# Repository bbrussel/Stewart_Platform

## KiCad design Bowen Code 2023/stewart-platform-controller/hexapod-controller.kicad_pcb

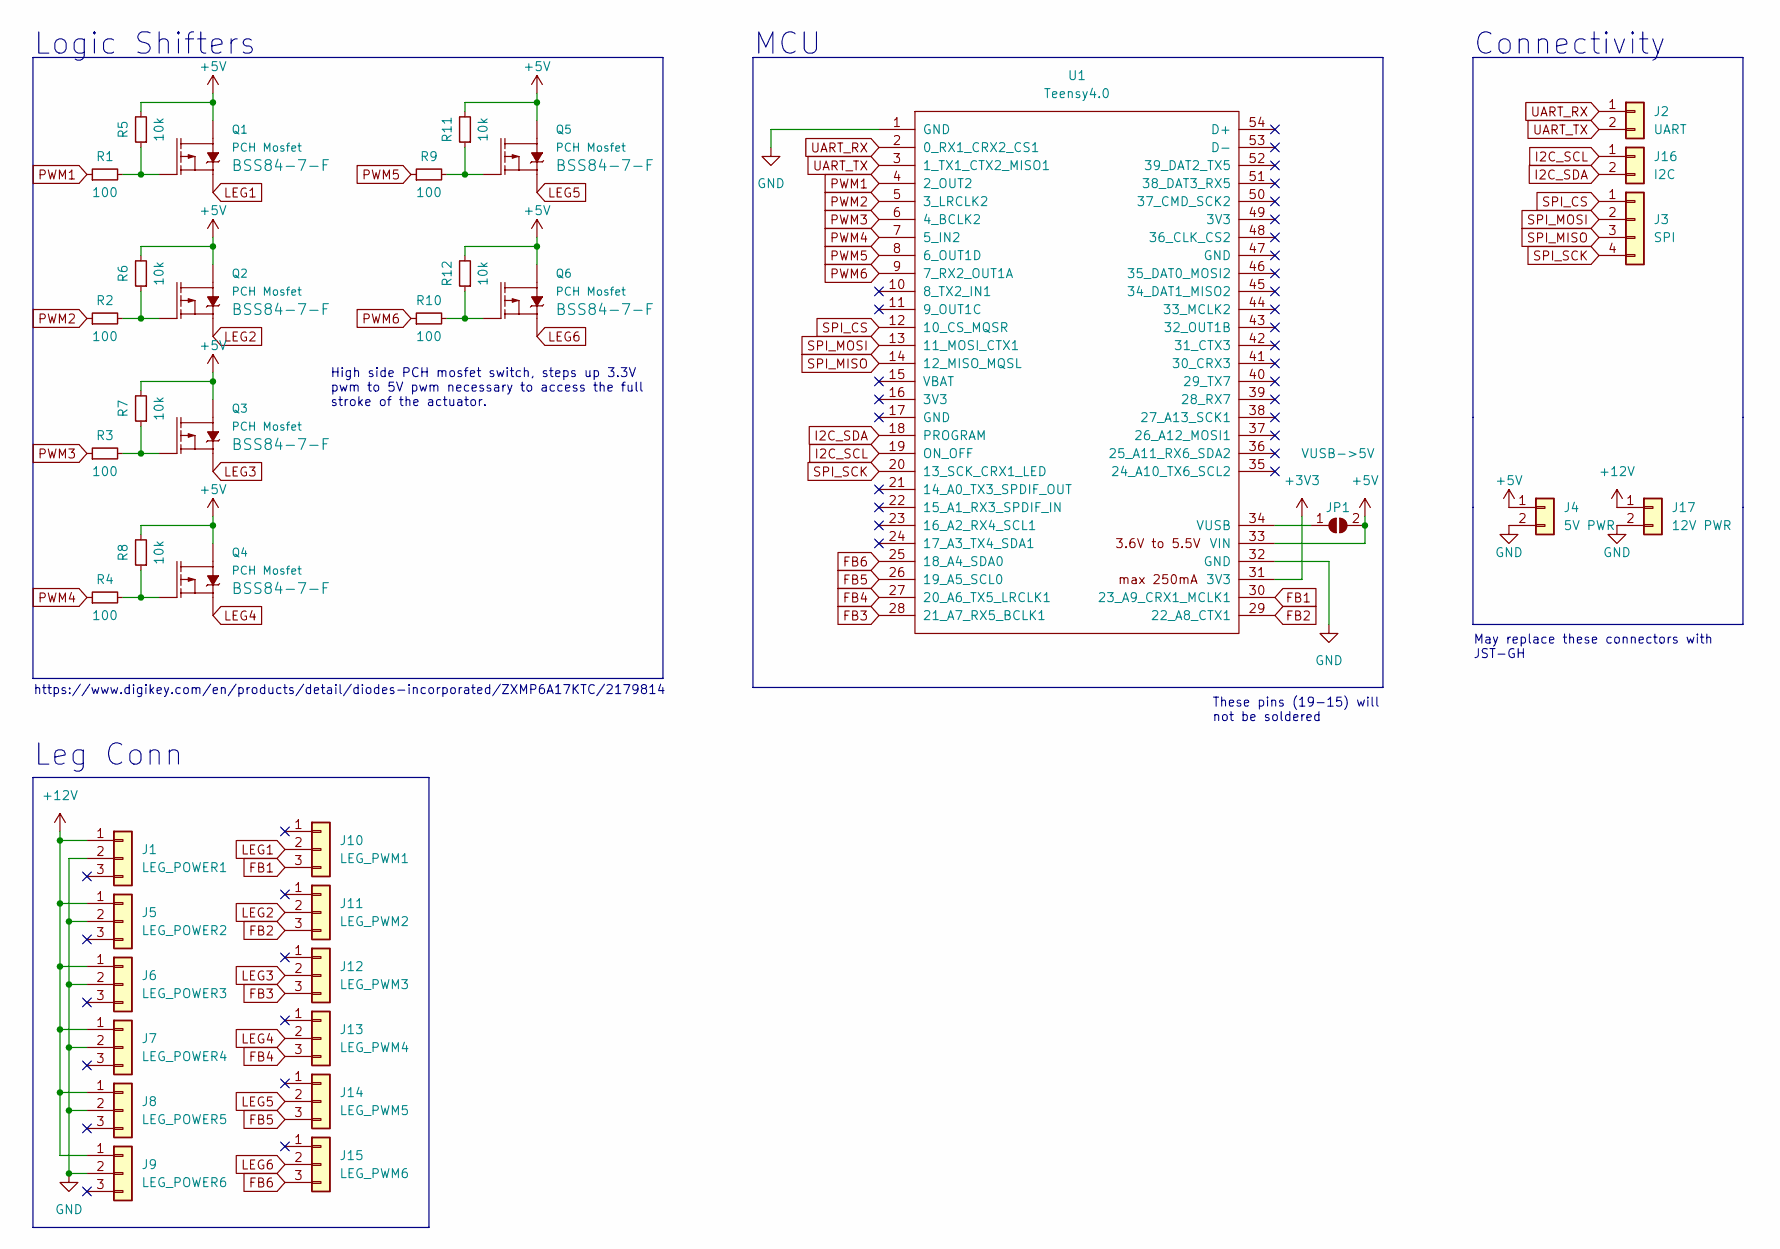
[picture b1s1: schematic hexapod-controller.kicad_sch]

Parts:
J1: LEG_POWER1; PinHeader_1x03_P2.54mm_Vertical
J2: UART; PinHeader_1x02_P2.54mm_Vertical
J3: SPI; PinHeader_1x04_P2.54mm_Vertical
J4: 5V PWR; PinHeader_1x02_P2.54mm_Vertical
J5: LEG_POWER2; PinHeader_1x03_P2.54mm_Vertical
J6: LEG_POWER3; PinHeader_1x03_P2.54mm_Vertical
J7: LEG_POWER4; PinHeader_1x03_P2.54mm_Vertical
J8: LEG_POWER5; PinHeader_1x03_P2.54mm_Vertical
J9: LEG_POWER6; PinHeader_1x03_P2.54mm_Vertical
J10: LEG_PWM1; PinHeader_1x03_P2.54mm_Vertical
J11: LEG_PWM2; PinHeader_1x03_P2.54mm_Vertical
J12: LEG_PWM3; PinHeader_1x03_P2.54mm_Vertical
J13: LEG_PWM4; PinHeader_1x03_P2.54mm_Vertical
J14: LEG_PWM5; PinHeader_1x03_P2.54mm_Vertical
J15: LEG_PWM6; PinHeader_1x03_P2.54mm_Vertical
J16: I2C; PinHeader_1x02_P2.54mm_Vertical
J17: 12V PWR; PinHeader_1x02_P2.54mm_Vertical
JP1: VUSB->5V; SolderJumper-2_P1.3mm_Open_TrianglePad1.0x1.5mm
Q1, Q2, Q3, Q4, Q5, Q6: PCH Mosfet; SOT-23-3
R1, R2, R3, R4, R9, R10: 100; R_0402_1005Metric
R5, R6, R7, R8, R11, R12: 10k; R_0402_1005Metric
U1: Teensy4.0; Teensy40_SMT

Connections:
+3V3: U1.31 (3V3)
+5V: J4.1, JP1.2 (B), Q1.3 (D), Q2.3 (D), Q3.3 (D), Q4.3 (D), Q5.3 (D), Q6.3 (D), R5.2, R6.2, R7.2, R8.2, R11.2, R12.2, U1.33 (VIN)
+12V: J1.1, J5.1, J6.1, J7.1, J8.1, J9.1, J17.1
FB1: J10.3, U1.30 (23_A9_CRX1_MCLK1)
FB2: J11.3, U1.29 (22_A8_CTX1)
FB3: J12.3, U1.28 (21_A7_RX5_BCLK1)
FB4: J13.3, U1.27 (20_A6_TX5_LRCLK1)
FB5: J14.3, U1.26 (19_A5_SCL0)
FB6: J15.3, U1.25 (18_A4_SDA0)
GND: J1.2, J4.2, J5.2, J6.2, J7.2, J8.2, J9.2, J17.2, U1.1 (GND), U1.32 (GND)
I2C_SCL: J16.1, U1.19 (ON_OFF)
I2C_SDA: J16.2, U1.18 (PROGRAM)
LEG1: J10.2, Q1.2 (S)
LEG2: J11.2, Q2.2 (S)
LEG3: J12.2, Q3.2 (S)
LEG4: J13.2, Q4.2 (S)
LEG5: J14.2, Q5.2 (S)
LEG6: J15.2, Q6.2 (S)
unnamed: JP1.1 (A), U1.34 (VUSB)
unnamed: Q1.1 (G), R1.2, R5.1
unnamed: Q2.1 (G), R2.2, R6.1
unnamed: Q3.1 (G), R3.2, R7.1
unnamed: Q4.1 (G), R4.2, R8.1
unnamed: Q5.1 (G), R9.2, R11.1
unnamed: Q6.1 (G), R10.2, R12.1
PWM1: R1.1, U1.4 (2_OUT2)
PWM2: R2.1, U1.5 (3_LRCLK2)
PWM3: R3.1, U1.6 (4_BCLK2)
PWM4: R4.1, U1.7 (5_IN2)
PWM5: R9.1, U1.8 (6_OUT1D)
PWM6: R10.1, U1.9 (7_RX2_OUT1A)
SPI_CS: J3.1, U1.12 (10_CS_MQSR)
SPI_MISO: J3.3, U1.14 (12_MISO_MQSL)
SPI_MOSI: J3.2, U1.13 (11_MOSI_CTX1)
SPI_SCK: J3.4, U1.20 (13_SCK_CRX1_LED)
UART_RX: J2.1, U1.2 (0_RX1_CRX2_CS1)
UART_TX: J2.2, U1.3 (1_TX1_CTX2_MISO1)

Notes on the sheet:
These pins (19-15) will not be soldered
Leg Conn
May replace these connectors with JST-GH
MCU
Connectivity
https://www.digikey.com/en/products/detail/diodes-incorporated/ZXMP6A17KTC/2179814
High side PCH mosfet switch, steps up 3.3V pwm to 5V pwm necessary to access the full stroke of the actuator.
Logic Shifters

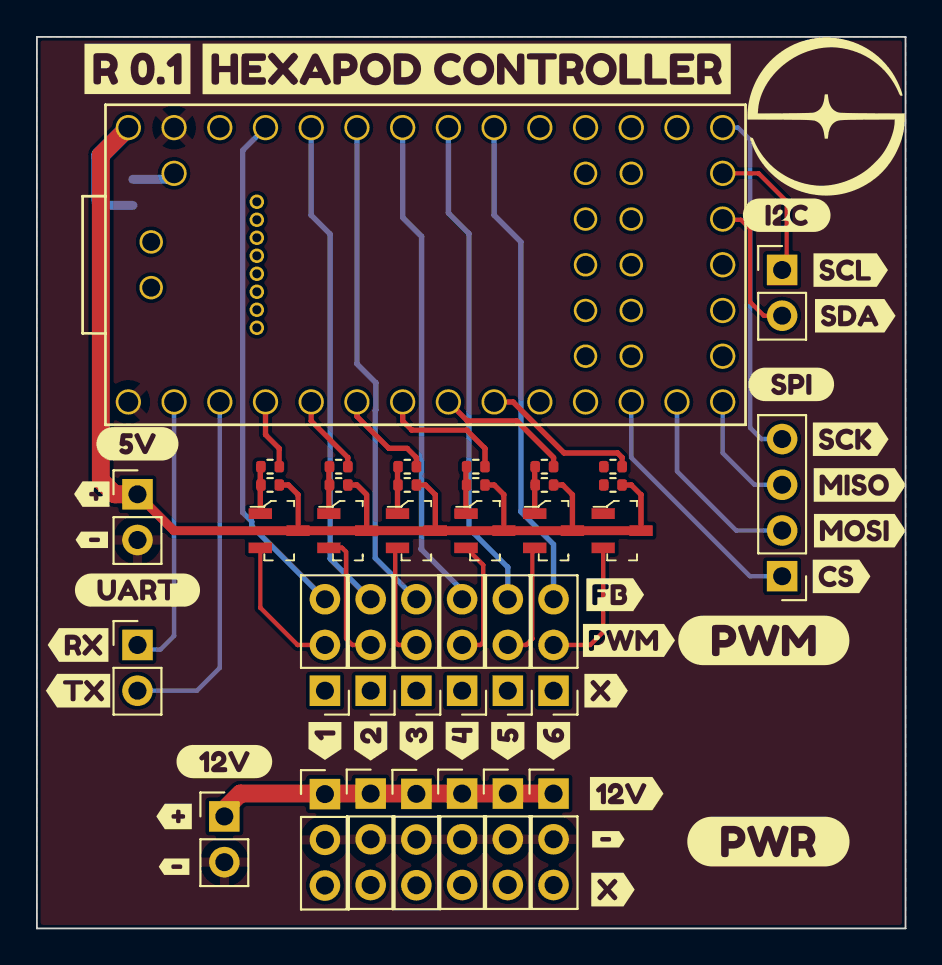
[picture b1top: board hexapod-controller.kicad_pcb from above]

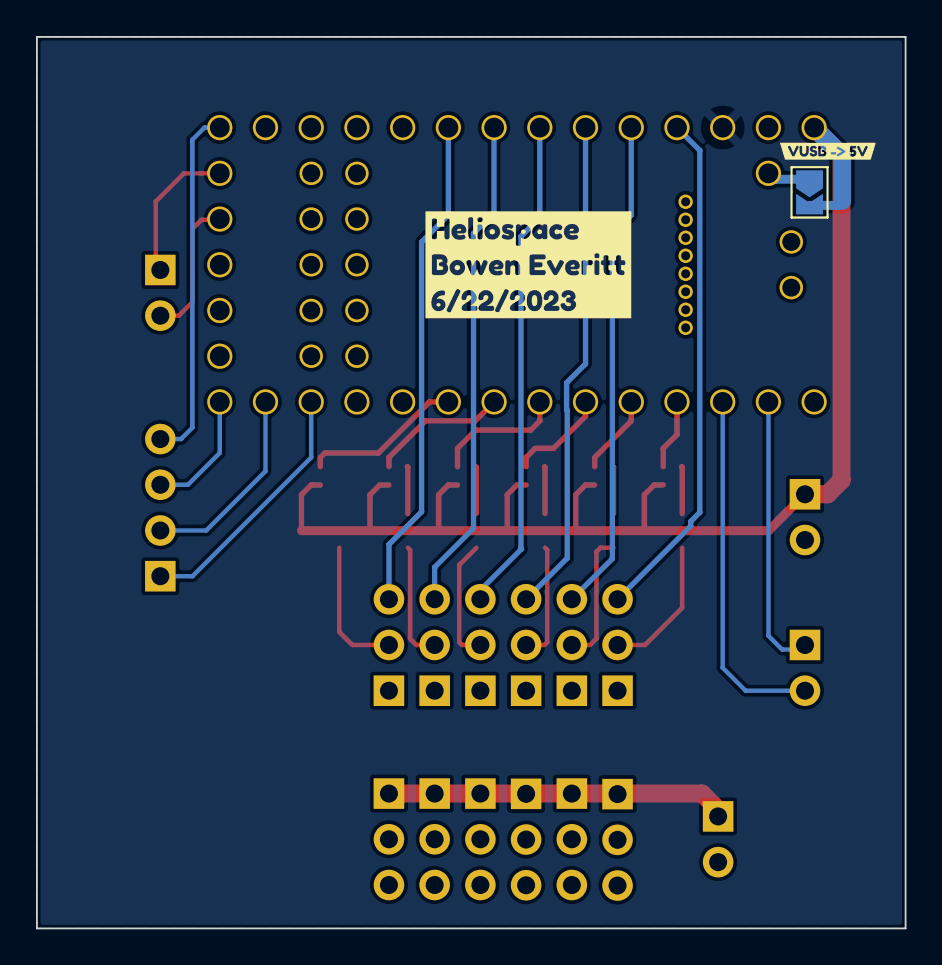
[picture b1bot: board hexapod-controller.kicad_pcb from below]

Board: 2 copper layers, 48.3 x 49.5 mm, 72 parts (3 on the bottom side), 36 nets.

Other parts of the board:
kibuzzard-64C9A29D: G***; kibuzzard-64C9A29D
kibuzzard-64CAC6D7: G***; kibuzzard-64CAC6D7
kibuzzard-64CAC6FD: G***; kibuzzard-64CAC6FD
kibuzzard-64CAC672: G***; kibuzzard-64CAC672
kibuzzard-64CAE08E: G***; kibuzzard-64CAE08E
kibuzzard-64CAE42C: G***; kibuzzard-64CAE42C
kibuzzard-64CAE079: G***; kibuzzard-64CAE079
kibuzzard-64CAE092, kibuzzard-64CAE092#2: G***; kibuzzard-64CAE092
kibuzzard-64CAE424: G***; kibuzzard-64CAE424
kibuzzard-64D674E6: G***; kibuzzard-64D674E6
kibuzzard-64D674ED: G***; kibuzzard-64D674ED
kibuzzard-64D681E8: G***; kibuzzard-64D681E8
kibuzzard-64D681EE: G***; kibuzzard-64D681EE
kibuzzard-64D681F4: G***; kibuzzard-64D681F4
kibuzzard-64D681FC: G***; kibuzzard-64D681FC
kibuzzard-64D6818E: G***; kibuzzard-64D6818E
kibuzzard-64D68196: G***; kibuzzard-64D68196
kibuzzard-6494A4C2: G***; kibuzzard-6494A4C2
kibuzzard-6494B50A: G***; kibuzzard-6494B50A
kibuzzard-6494B447: G***; kibuzzard-6494B447
kibuzzard-649486BE: G***; kibuzzard-649486BE
kibuzzard-649486D4: G***; kibuzzard-649486D4
kibuzzard-649486DA, kibuzzard-649486DA#2: G***; kibuzzard-649486DA
kibuzzard-649486E4: G***; kibuzzard-649486E4
kibuzzard-649486EE: G***; kibuzzard-649486EE
kibuzzard-6494861E: G***; kibuzzard-6494861E
kibuzzard-6494862C: G***; kibuzzard-6494862C
kibuzzard-6494871C: G***; kibuzzard-6494871C
kibuzzard-64948619: G***; kibuzzard-64948619
kibuzzard-64948622: G***; kibuzzard-64948622
kibuzzard-64948628: G***; kibuzzard-64948628
kibuzzard-64948630: G***; kibuzzard-64948630
kibuzzard-64948713: G***; kibuzzard-64948713

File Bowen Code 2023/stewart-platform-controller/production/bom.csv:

Designator,Footprint,Quantity,Value,LCSC Part #
J14,PinHeader_1x03_P2.54mm_Vertical,1,LEG_PWM5,
J2,PinHeader_1x02_P2.54mm_Vertical,1,UART,
J12,PinHeader_1x03_P2.54mm_Vertical,1,LEG_PWM3,
U2,TSSOP-20_W4.4mm,1,TXB0108,
J15,PinHeader_1x03_P2.54mm_Vertical,1,LEG_PWM6,
J10,PinHeader_1x03_P2.54mm_Vertical,1,LEG_PWM1,
J11,PinHeader_1x03_P2.54mm_Vertical,1,LEG_PWM2,
J17,PinHeader_1x02_P2.54mm_Vertical,1,12V PWR,
J1,PinHeader_1x03_P2.54mm_Vertical,1,LEG_POWER1,
J16,PinHeader_1x02_P2.54mm_Vertical,1,I2C,
J4,PinHeader_1x02_P2.54mm_Vertical,1,5V PWR,
U1,Teensy40_SMT,1,Teensy4.0,
J7,PinHeader_1x03_P2.54mm_Vertical,1,LEG_POWER4,
J6,PinHeader_1x03_P2.54mm_Vertical,1,LEG_POWER3,
J9,PinHeader_1x03_P2.54mm_Vertical,1,LEG_POWER6,
J3,PinHeader_1x04_P2.54mm_Vertical,1,SPI,
J13,PinHeader_1x03_P2.54mm_Vertical,1,LEG_PWM4,
J8,PinHeader_1x03_P2.54mm_Vertical,1,LEG_POWER5,
J5,PinHeader_1x03_P2.54mm_Vertical,1,LEG_POWER2,
JP1,SolderJumper-2_P1.3mm_Open_TrianglePad1.0x1.5mm,1,VUSB->5V,

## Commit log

2025-09-30 Updates to platform geometry variables
2025-10-15 added .gitignore
2025-10-15 updates to arduino driver code and python leg length demo code
2025-10-15 updated leg length algo to allow for multiple poses
2025-10-15 updates to multi position demo in leg lengths algo code
2025-10-29 Added calc for max and min platform z coord
2025-10-30 Added stroke % to graphic
2025-11-12 UPdated screen output for actuation faults and warning lengths
2025-11-13 refactored code. Added range of motion sweeping function
2025-11-19 Updated for firgellie actuator driver commands
2025-12-09 Push before SLO trip
2026-01-12 Added config file and config file stamping to images
2026-01-13 Update to viewing angle selection in 3D plots
